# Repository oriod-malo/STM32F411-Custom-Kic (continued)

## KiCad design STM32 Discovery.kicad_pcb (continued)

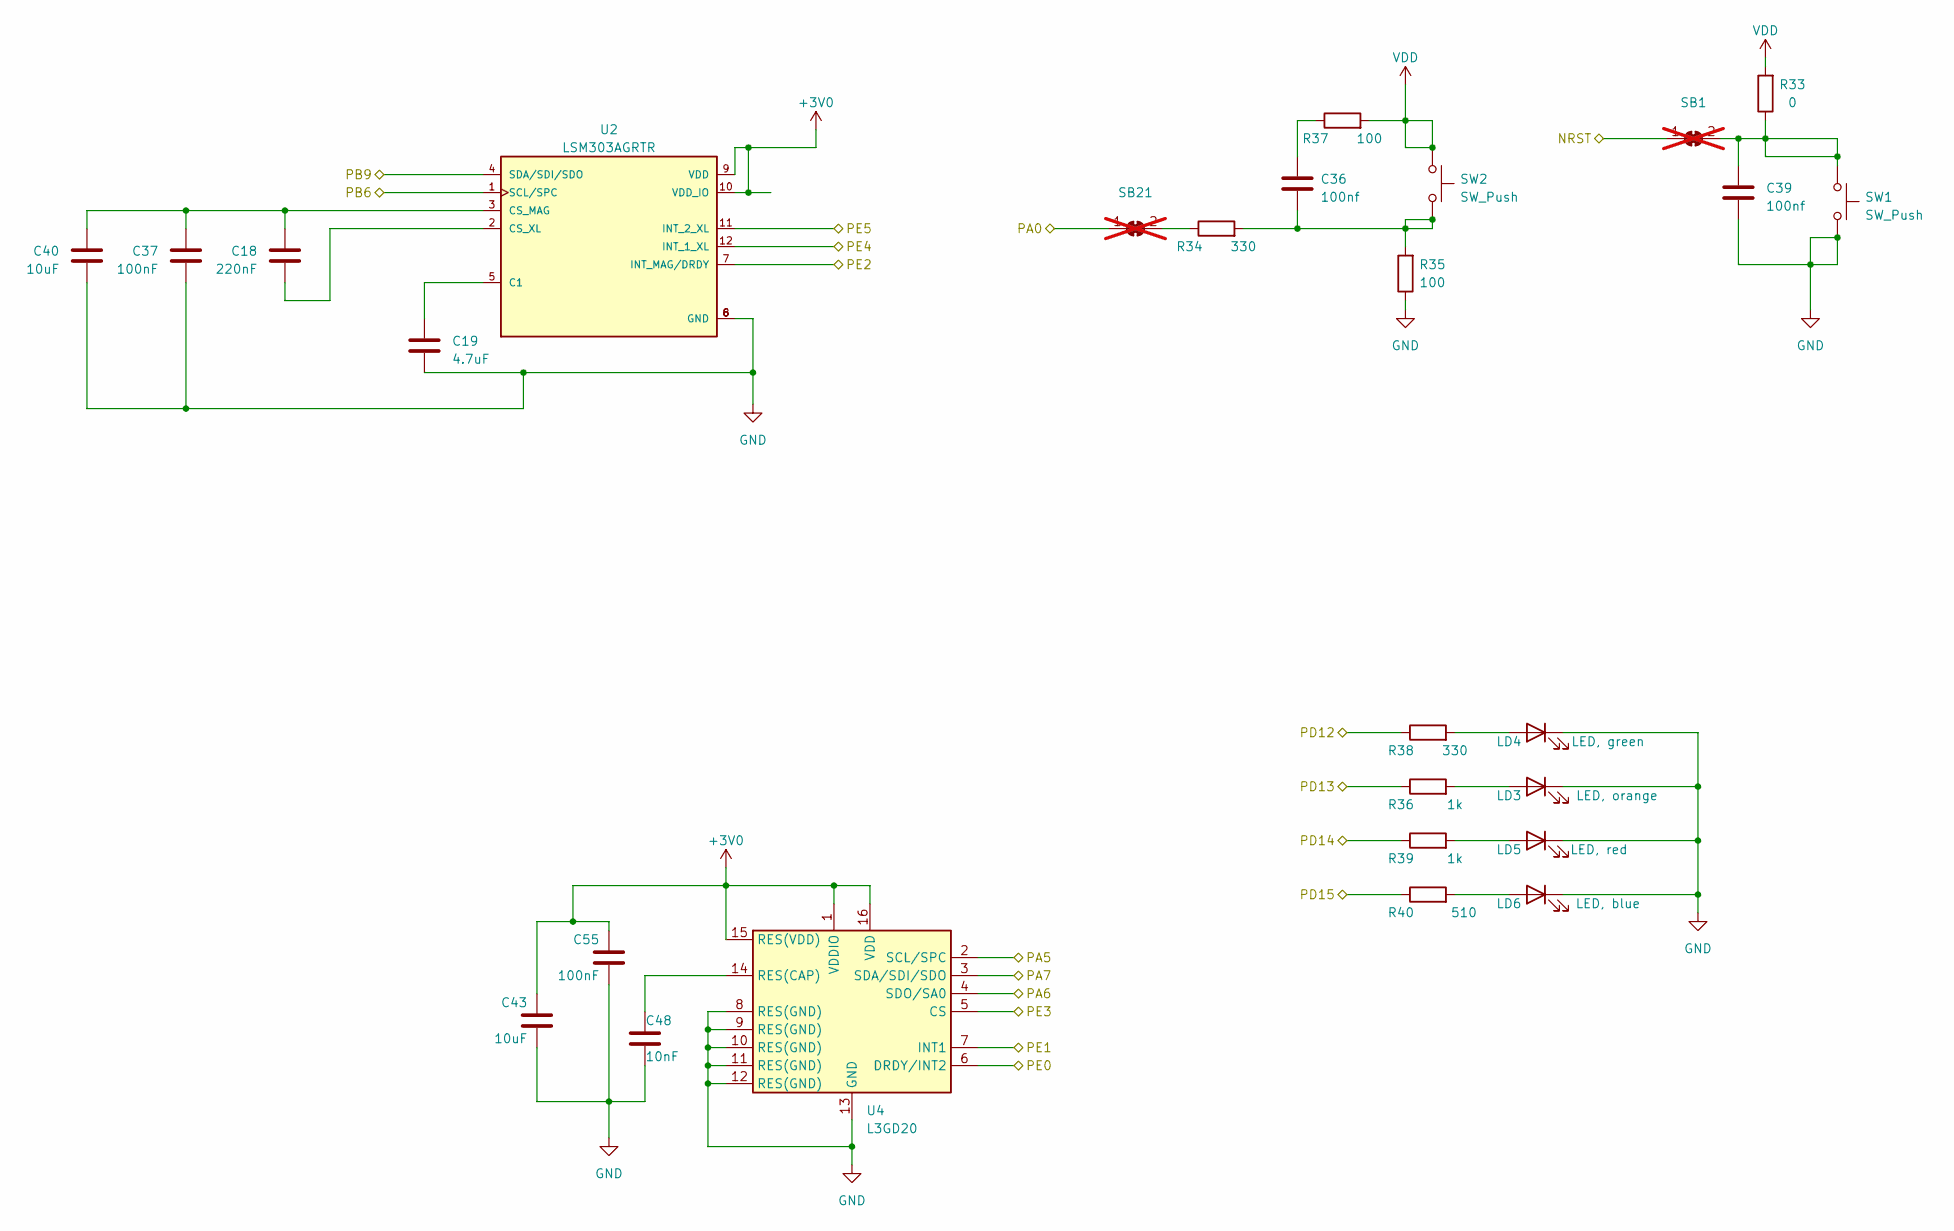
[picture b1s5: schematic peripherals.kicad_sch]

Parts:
C18: 220nF; C_0402_1005Metric
C19: 4.7uF; C_0402_1005Metric
C36, C39: 100nf; C_0402_1005Metric
C37, C55: 100nF; C_0402_1005Metric
C40, C43: 10uF; C_0402_1005Metric
C48: 10nF; C_0402_1005Metric
LD3: LED, orange; LED_0402_1005Metric
LD4: LED, green; LED_0402_1005Metric
LD5: LED, red; LED_0402_1005Metric
LD6: LED, blue; LED_0402_1005Metric
R33: 0; R_0402_1005Metric
R34, R38: 330; R_0402_1005Metric
R35, R37: 100; R_0402_1005Metric
R36, R39: 1k; R_0402_1005Metric
R40: 510; R_0402_1005Metric
SB1, SB21: SolderJumper_2_Bridged; SolderJumper-2_P1.3mm_Bridged2Bar_Pad1.0x1.5mm; not fitted
SW1, SW2: SW_Push; SW_Push_1P1T_NO_6x6mm_H9.5mm
U2: LSM303AGRTR; LGA12R50P_200X200X100
U4: L3GD20; LGA-16_4x4mm_P0.65mm_LayoutBorder4x4y

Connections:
+3V0: C43.1, C55.1, U2.9 (VDD), U2.10 (VDD_IO), U4.1 (VDDIO), U4.15 (RES(VDD)), U4.16 (VDD); also elsewhere on the board
/NRST: SB1.1 (A); also elsewhere on the board
/PA0: SB21.1 (A); also elsewhere on the board
/PA5: U4.2 (SCL/SPC); also elsewhere on the board
/PA6: U4.4 (SDO/SA0); also elsewhere on the board
/PA7: U4.3 (SDA/SDI/SDO); also elsewhere on the board
/PB6: U2.1 (SCL/SPC); also elsewhere on the board
/PB9: U2.4 (SDA/SDI/SDO); also elsewhere on the board
/PD12: R38.1; also elsewhere on the board
/PD13: R36.1; also elsewhere on the board
/PD14: R39.1; also elsewhere on the board
/PD15: R40.1; also elsewhere on the board
/PE0: U4.6 (DRDY/INT2); also elsewhere on the board
/PE1: U4.7 (INT1); also elsewhere on the board
/PE2: U2.7 (INT_MAG/DRDY); also elsewhere on the board
/PE3: U4.5 (CS); also elsewhere on the board
/PE4: U2.12 (INT_1_XL); also elsewhere on the board
/PE5: U2.11 (INT_2_XL); also elsewhere on the board
GND: C19.2, C37.2, C39.2, C40.2, C43.2, C48.2, C55.2, LD3.1 (K), LD4.1 (K), LD5.1 (K), LD6.1 (K), R35.1, SW1.2, U2.6 (GND), U2.8 (GND), U4.8 (RES(GND)), U4.9 (RES(GND)), U4.10 (RES(GND)), U4.11 (RES(GND)), U4.12 (RES(GND)), U4.13 (GND); also elsewhere on the board
unnamed: C36.1, R37.1
unnamed: C36.2, R34.2, R35.2, SW2.2
unnamed: LD3.2 (A), R36.2
unnamed: LD4.2 (A), R38.2
unnamed: LD5.2 (A), R39.2
unnamed: LD6.2 (A), R40.2
unnamed: C39.1, R33.1, SB1.2 (B), SW1.1
unnamed: R34.1, SB21.2 (B)
unnamed: C19.1, U2.5 (C1)
unnamed: C18.1, C37.1, C40.1, U2.3 (CS_MAG)
unnamed: C18.2, U2.2 (CS_XL)
unnamed: C48.1, U4.14 (RES(CAP))
VDD: R33.2, R37.2, SW2.1; also elsewhere on the board

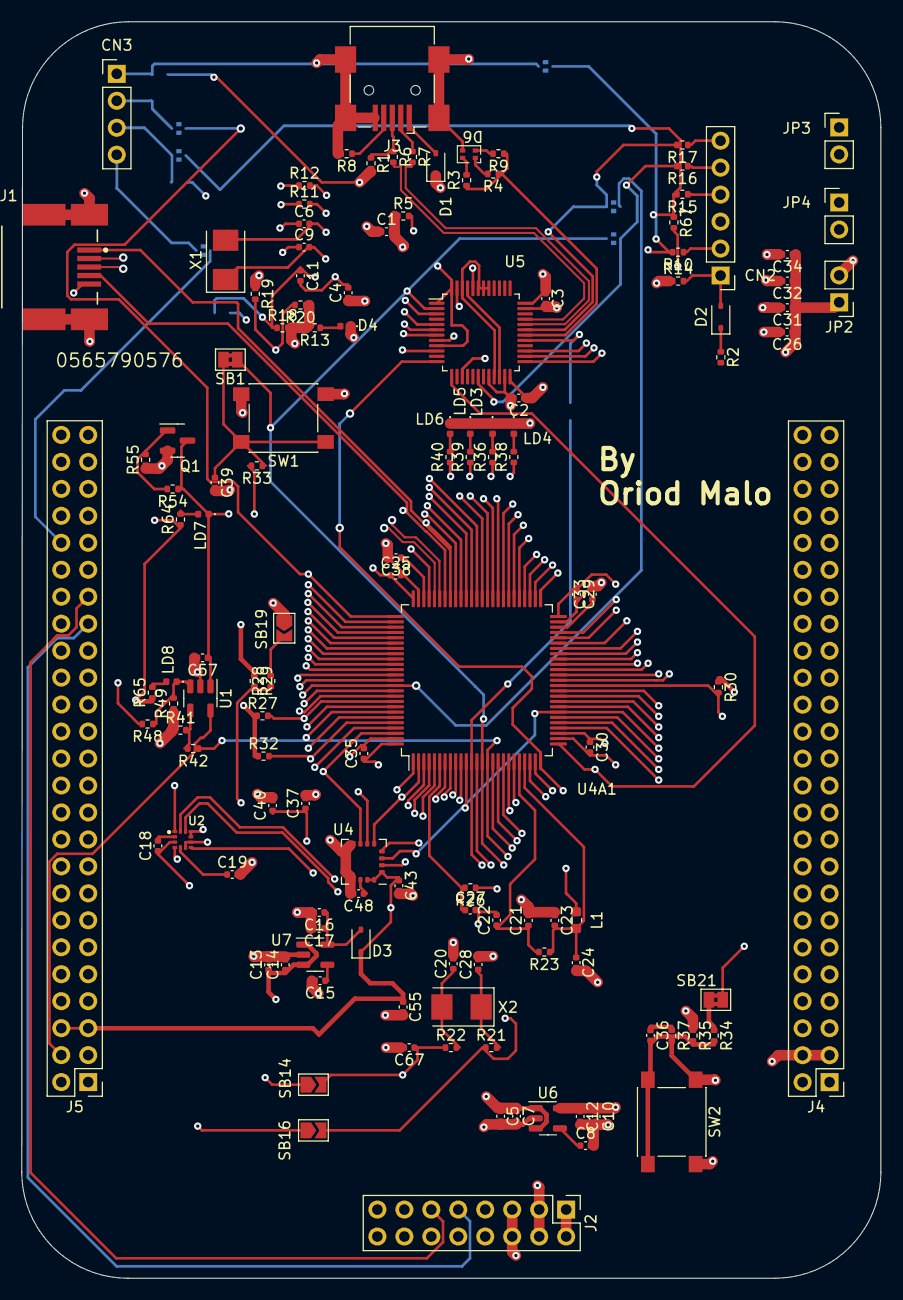
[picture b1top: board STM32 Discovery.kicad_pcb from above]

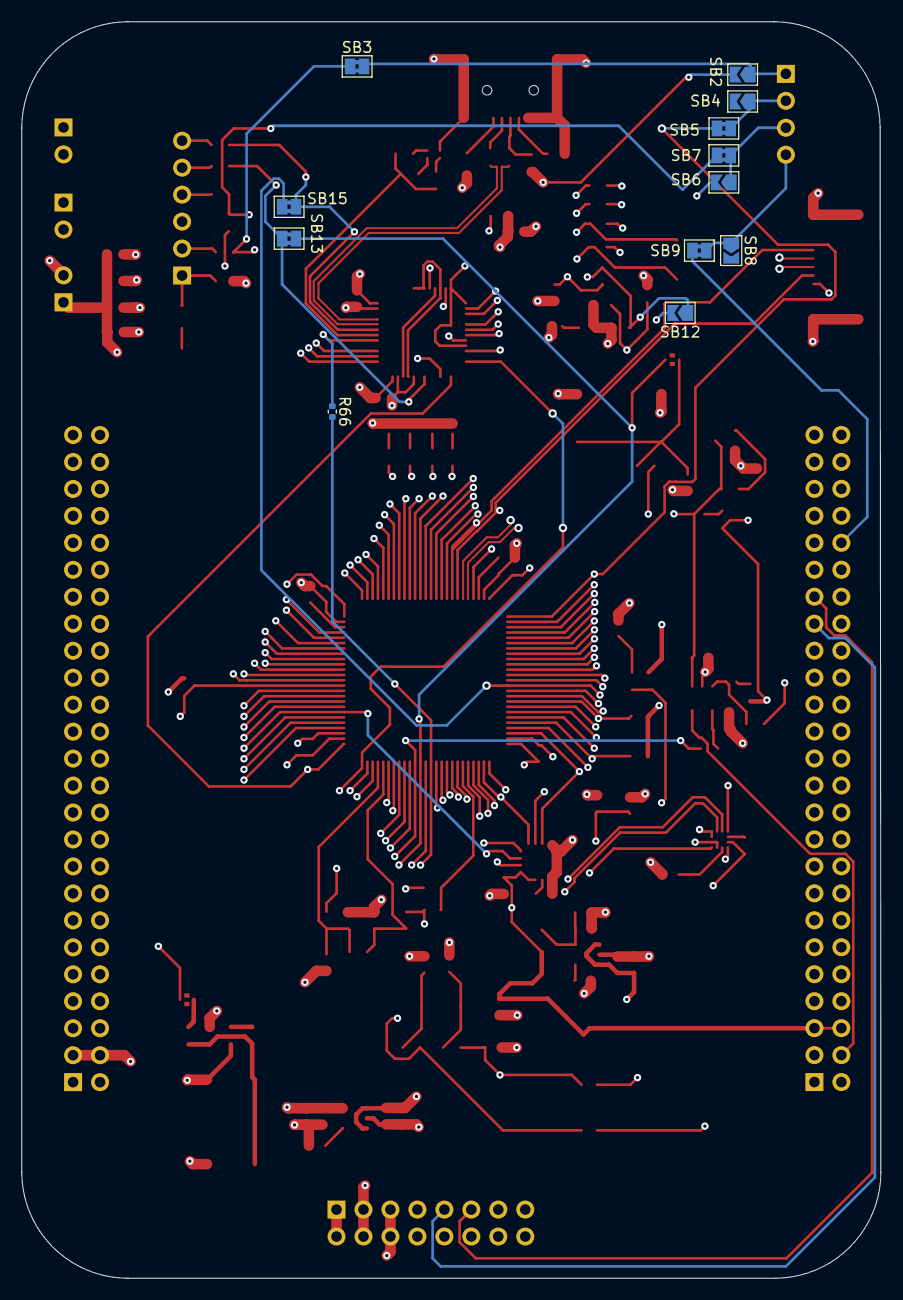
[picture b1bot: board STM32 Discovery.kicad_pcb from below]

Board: 6 copper layers, 80.9 x 118.4 mm, 142 parts (12 on the bottom side), 154 nets.
